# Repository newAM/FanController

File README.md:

## IR Fan Controller

### What is it?
This project is an Ethernet connected IR remote control for a the Seville classics ultra slimline tower fan, but it can be easily adapted to control other IR devices.  

### Why?
To connect my fan to Home Assistant so that it can turn on automatically when it gets hot, and turn off automatically when I leave home.

#### Why PoE?
Wireless home automation devices often make sense only when they are battery powered, if a power cable needs to be run it can carry data too.  Designing a low power wireless device is far more complicated than designing a wired device and running an Ethernet cable.

## Overview
Home Assistant → MQTT Broker → W5100 (Ethernet) → ATMega328P (MCU) → IR LED

The controller takes the states of the power, oscillation, mode, timer, and speed from Home Assistant.  These values are used to build the IR code then transmit it through the IR LED.

## Project Contents
* FanController_ArduinoCode - firmware for the ATMega328P
* FanController_Guide - reverse engineering guide for IR codes
* FanController_HomeAssistant - example Home Assistant configuration
* FanController_KiCAD - schematic and PCB
* FanController_Media - photos

## Software Used
* [KiCad](http://kicad.org/)
* [Arduino IDE](https://www.arduino.cc/en/Main/Software)
* [OpenSCAD](http://www.openscad.org/)
* [Libre Office](https://www.libreoffice.org/)
* [Home Assistant](https://www.home-assistant.io/)

### Arduino Libraries used
* [Arduino MQTT Client](https://github.com/knolleary/pubsubclient)

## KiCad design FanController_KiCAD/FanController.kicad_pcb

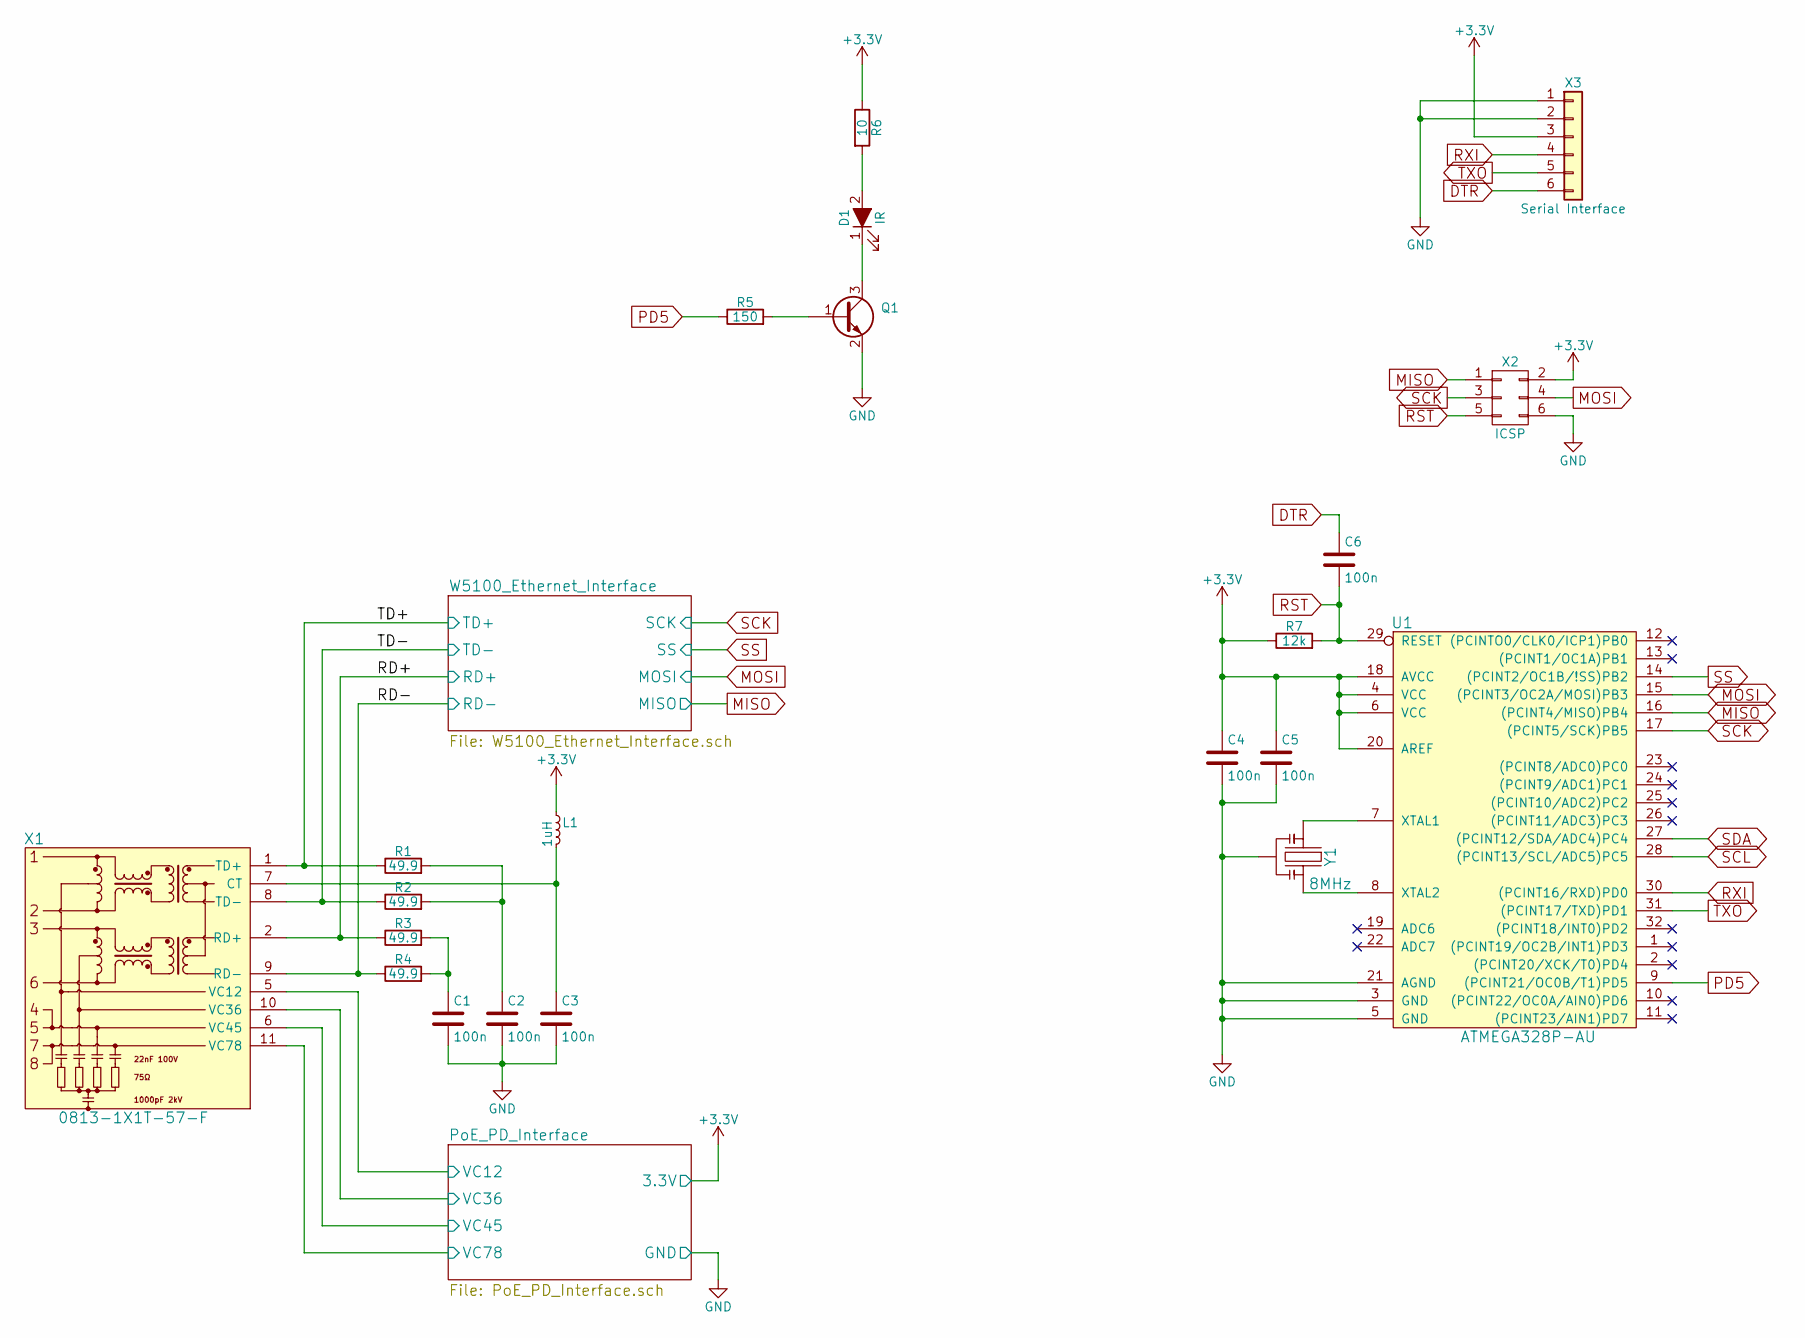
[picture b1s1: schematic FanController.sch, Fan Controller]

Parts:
C1, C2, C3, C4, C5, C6: 100n; C_0603; DigiKey Part Number 1276-1005-1-ND
D1: IR; LED_D5.0mm
L1: 1uH; C_0603; DigiKey Part Number 445-3163-1-ND
Q1: Q_NPN_BEC; SOT-23; DigiKey Part Number MMBT3904LT1GOSCT-ND
R1, R2, R3, R4: 49.9; R_0805; DigiKey Part Number RNCP0805FTD49R9CT-ND
R5: 150; R_0603; Tolerance 1%; DigiKey Part Number 311-150HRCT-ND
R6: 10; R_0805; DigiKey Part Number RNCP0805FTD10R0CT-ND
R7: 12k; R_0603; Tolerance 1%; DigiKey Part Number 311-12.0KHRCT-ND
U1: ATMEGA328P-AU; TQFP-32_7x7mm_Pitch0.8mm; DigiKey Part Number ATMEGA328P-AU-ND
X1: 0813-1X1T-57-F; 0813-1X1T-57-F_RJ45-Jack; DigiKey Part Number 507-1421-ND
X2: ICSP; Pin_Header_Straight_2x03_Pitch2.54mm
X3: Serial Interface; Pin_Header_Angled_1x06_Pitch2.54mm
Y1: 8MHz; CERALOCK_CSTCE_Resonator; DigiKey Part Number 490-1195-1-ND

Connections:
+3V3: C4.1, C5.1, L1.1, R6.1, R7.1, U1.4 (VCC), U1.6 (VCC), U1.18 (AVCC), U1.20 (AREF), X2.2, X3.3; also elsewhere on the board
/PoE_PD_Interface/VC12: X1.5 (VC12); also elsewhere on the board
/PoE_PD_Interface/VC36: X1.10 (VC36); also elsewhere on the board
/PoE_PD_Interface/VC45: X1.6 (VC45); also elsewhere on the board
/PoE_PD_Interface/VC78: X1.11 (VC78); also elsewhere on the board
/RD+: R3.1, X1.2 (RD+); also elsewhere on the board
/RD-: R4.1, X1.9 (RD-); also elsewhere on the board
/TD+: R1.1, X1.1 (TD+); also elsewhere on the board
/TD-: R2.1, X1.8 (TD-); also elsewhere on the board
DTR: C6.1, X3.6
GND: C1.2, C2.2, C3.2, C4.2, C5.2, Q1.2 (E), U1.3 (GND), U1.5 (GND), U1.21 (AGND), X2.6, X3.1, X3.2, Y1.2; also elsewhere on the board
MISO: U1.16 ((PCINT4/MISO)PB4), X2.1; also elsewhere on the board
MOSI: U1.15 ((PCINT3/OC2A/MOSI)PB3), X2.4; also elsewhere on the board
unnamed: C1.1, R3.2, R4.2
unnamed: C2.1, R1.2, R2.2
unnamed: C3.1, L1.2, X1.7 (CT)
unnamed: D1.1 (K), Q1.3 (C)
unnamed: D1.2 (A), R6.2
unnamed: Q1.1 (B), R5.2
unnamed: U1.7 (XTAL1), Y1.1
unnamed: U1.8 (XTAL2), Y1.3
PD5: R5.1, U1.9 ((PCINT21/OC0B/T1)PD5)
RST: C6.2, R7.2, U1.29 (RESET), X2.5
RXI: U1.30 ((PCINT16/RXD)PD0), X3.4
SCK: U1.17 ((PCINT5/SCK)PB5), X2.3; also elsewhere on the board
SS: U1.14 ((PCINT2/OC1B/!SS)PB2); also elsewhere on the board
TXO: U1.31 ((PCINT17/TXD)PD1), X3.5

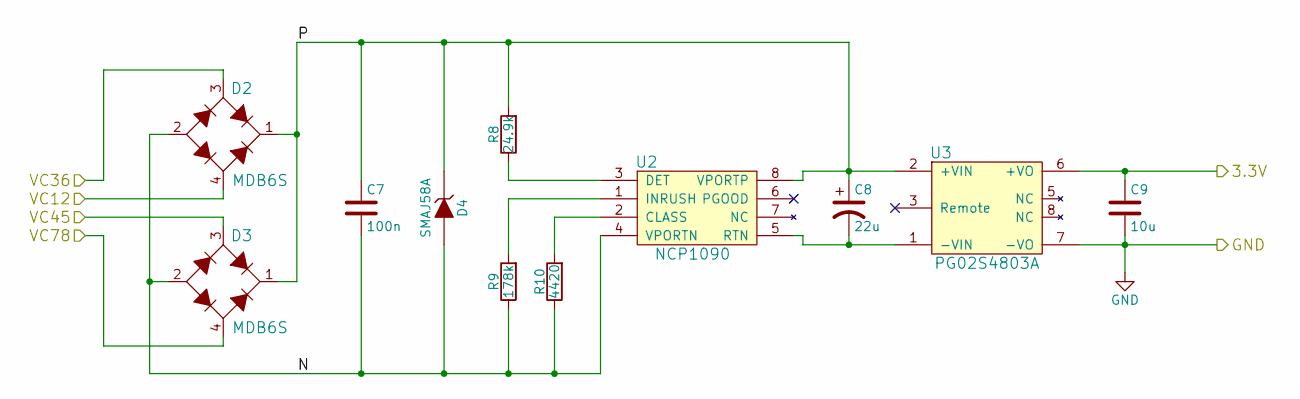
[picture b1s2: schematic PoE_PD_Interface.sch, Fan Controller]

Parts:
C7: 100n; C_0805; DigiKey Part Number 1276-6840-1-ND
C8: 22u; CP_Radial_D5.0mm_P2.00mm; DigiKey Part Number 493-12798-1-ND
C9: 10u; C_0805; DigiKey Part Number 1276-6456-1-ND
D2, D3: MDB6S; Micro-DIP-4; DigiKey Part Number MDB6SFSCT-ND
D4: SMAJ58A; D_SMA; DigiKey Part Number SMAJ58A-E3/61GICT-ND
R8: 24.9k; R_0603; DigiKey Part Number 311-24.9KHRCT-ND
R9: 178k; R_0603; DigiKey Part Number 311-178KHRCT-ND
R10: 4420; R_0603; DigiKey Part Number 311-4.42KHRCT-ND
U2: NCP1090; SOIC-8_3.9x4.9mm_Pitch1.27mm; DigiKey Part Number NCP1090DGOS-ND
U3: PG02S4803A; PG02S; DigiKey Part Number 941-1185-ND

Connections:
+3V3: C9.1, U3.6 (+VO); also elsewhere on the board
/PoE_PD_Interface/N: C7.2, D2.2 (-), D3.2 (-), D4.2 (A), R9.1, R10.1, U2.4 (VPORTN)
/PoE_PD_Interface/P: C7.1, C8.1, D2.1 (+), D3.1 (+), D4.1 (K), R8.2, U2.8 (VPORTP), U3.2 (+VIN)
/PoE_PD_Interface/VC12: D2.4 (AC2); also elsewhere on the board
/PoE_PD_Interface/VC36: D2.3 (AC1); also elsewhere on the board
/PoE_PD_Interface/VC45: D3.3 (AC1); also elsewhere on the board
/PoE_PD_Interface/VC78: D3.4 (AC2); also elsewhere on the board
GND: C9.2, U3.7 (-VO); also elsewhere on the board
unnamed: C8.2, U2.5 (RTN), U3.1 (-VIN)
unnamed: R8.1, U2.3 (DET)
unnamed: R9.2, U2.1 (INRUSH)
unnamed: R10.2, U2.2 (CLASS)

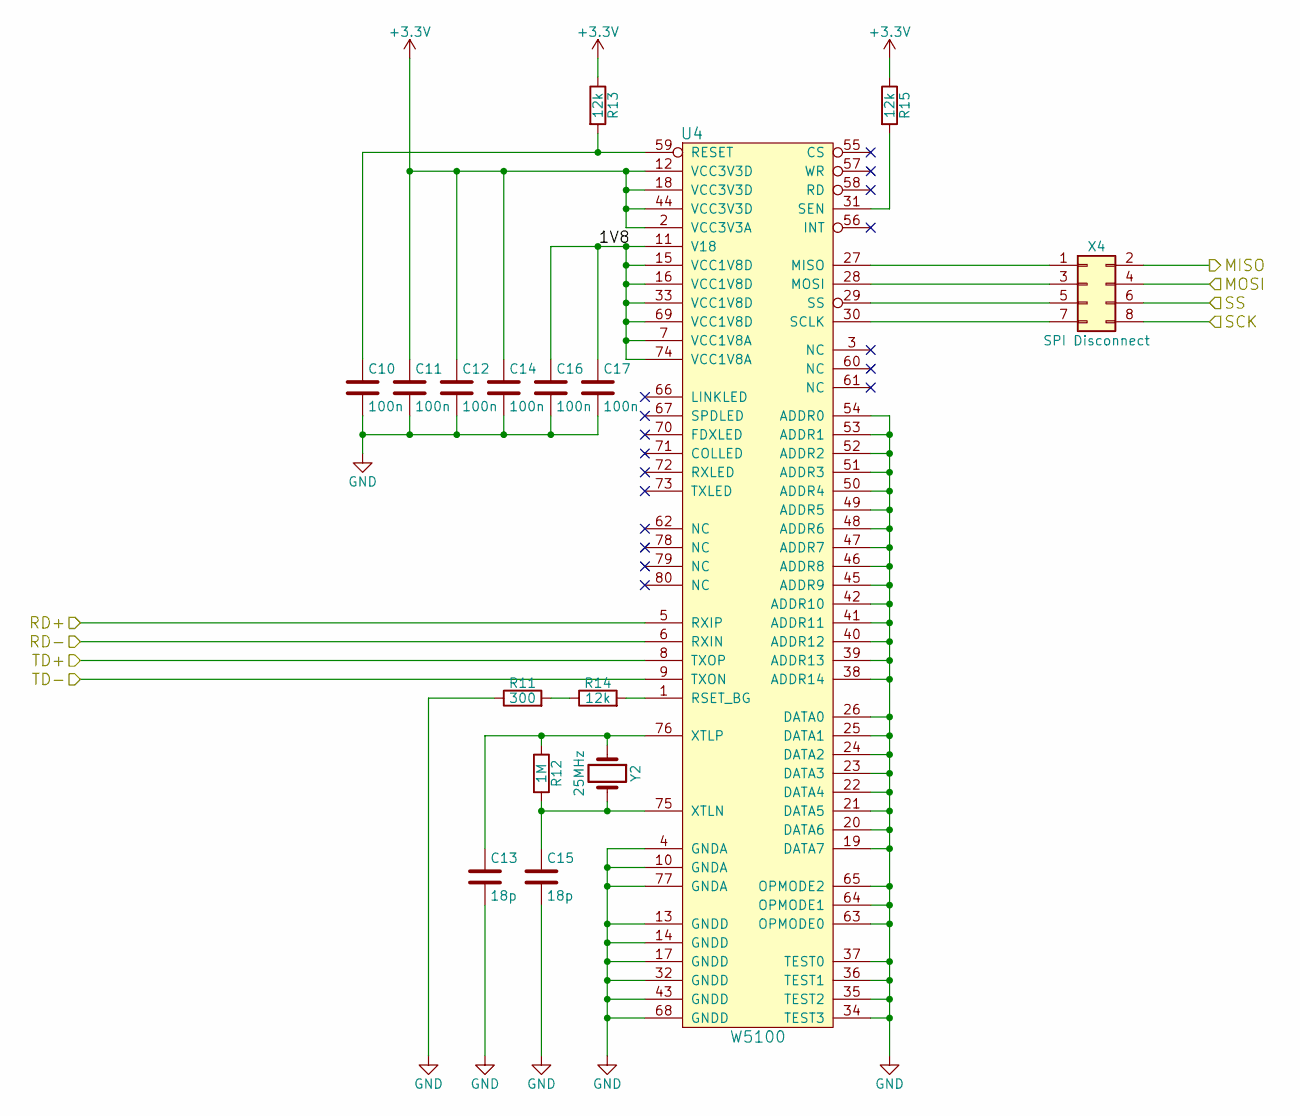
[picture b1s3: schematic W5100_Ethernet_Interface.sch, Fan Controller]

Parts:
C10, C11, C12, C14, C16, C17: 100n; C_0603; DigiKey Part Number 1276-1005-1-ND
C13, C15: 18p; C_0603; DigiKey Part Number 1276-1089-1-ND
R11: 300; R_0603; Tolerance 1%; DigiKey Part Number 311-300HRCT-ND
R12: 1M; R_0603; Tolerance 1%; DigiKey Part Number 311-1.00MHRCT-ND
R13, R14, R15: 12k; R_0603; Tolerance 1%; DigiKey Part Number 311-12.0KHRCT-ND
U4: W5100; LQFP-80_10x10mm_Pitch0.4mm; DigiKey Part Number 1278-1002-ND
X4: SPI Disconnect; Pin_Header_Straight_2x04_Pitch2.54mm
Y2: 25MHz; Crystal_SMD_HC49-SD; DigiKey Part Number 535-10235-1-ND

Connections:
+3V3: C11.1, C12.1, C14.1, R13.1, R15.1, U4.2 (VCC3V3A), U4.12 (VCC3V3D), U4.18 (VCC3V3D), U4.44 (VCC3V3D); also elsewhere on the board
/RD+: U4.5 (RXIP); also elsewhere on the board
/RD-: U4.6 (RXIN); also elsewhere on the board
/TD+: U4.8 (TXOP); also elsewhere on the board
/TD-: U4.9 (TXON); also elsewhere on the board
/W5100_Ethernet_Interface/1V8: C16.1, C17.1, U4.7 (VCC1V8A), U4.11 (V18), U4.15 (VCC1V8D), U4.16 (VCC1V8D), U4.33 (VCC1V8D), U4.69 (VCC1V8D), U4.74 (VCC1V8A)
GND: C10.2, C11.2, C12.2, C13.2, C14.2, C15.2, C16.2, C17.2, R11.1, U4.4 (GNDA), U4.10 (GNDA), U4.13 (GNDD), U4.14 (GNDD), U4.17 (GNDD), U4.19 (DATA7), U4.20 (DATA6), U4.21 (DATA5), U4.22 (DATA4), U4.23 (DATA3), U4.24 (DATA2), U4.25 (DATA1), U4.26 (DATA0), U4.32 (GNDD), U4.34 (TEST3), U4.35 (TEST2), U4.36 (TEST1), U4.37 (TEST0), U4.38 (ADDR14), U4.39 (ADDR13), U4.40 (ADDR12), U4.41 (ADDR11), U4.42 (ADDR10), U4.43 (GNDD), U4.45 (ADDR9), U4.46 (ADDR8), U4.47 (ADDR7), U4.48 (ADDR6), U4.49 (ADDR5), U4.50 (ADDR4), U4.51 (ADDR3), U4.52 (ADDR2), U4.53 (ADDR1), U4.54 (ADDR0), U4.63 (OPMODE0), U4.64 (OPMODE1), U4.65 (OPMODE2), U4.68 (GNDD), U4.77 (GNDA); also elsewhere on the board
MISO: X4.2; also elsewhere on the board
MOSI: X4.4; also elsewhere on the board
unnamed: C10.1, R13.2, U4.59 (RESET)
unnamed: C13.1, R12.1, U4.76 (XTLP), Y2.1
unnamed: C15.1, R12.2, U4.75 (XTLN), Y2.2
unnamed: R11.2, R14.1
unnamed: R14.2, U4.1 (RSET_BG)
unnamed: R15.2, U4.31 (SEN)
unnamed: U4.27 (MISO), X4.1
unnamed: U4.28 (MOSI), X4.3
unnamed: U4.29 (SS), X4.5
unnamed: U4.30 (SCLK), X4.7
SCK: X4.8; also elsewhere on the board
SS: X4.6; also elsewhere on the board

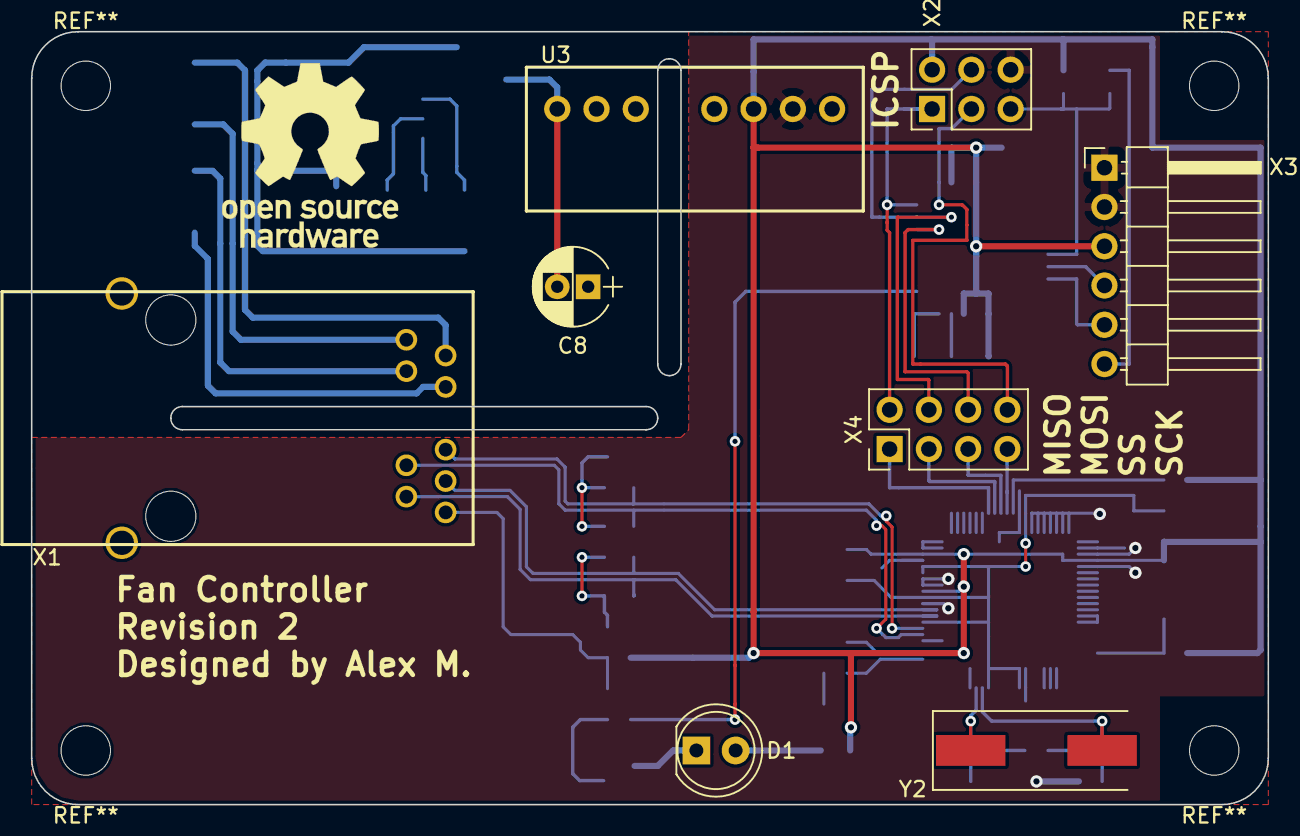
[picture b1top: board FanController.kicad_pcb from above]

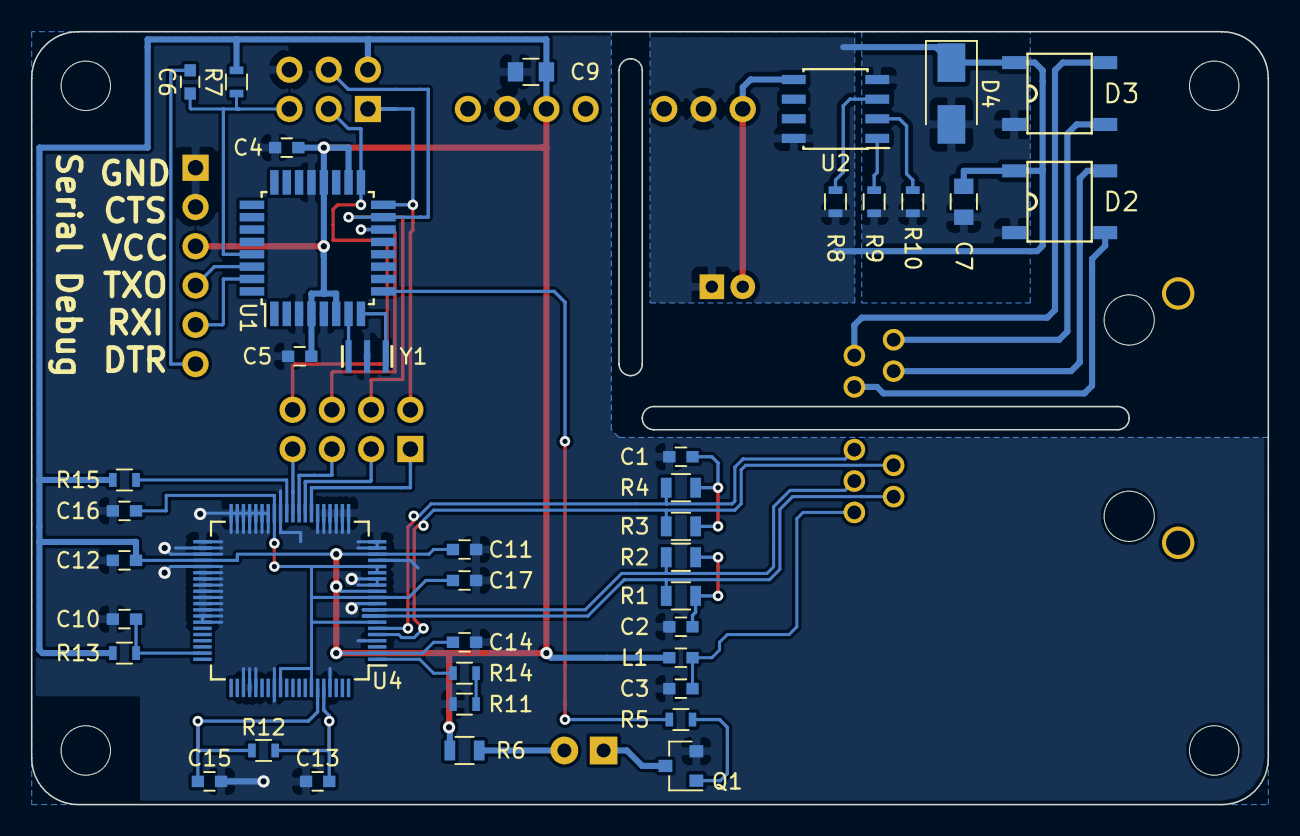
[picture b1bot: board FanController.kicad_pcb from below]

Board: 2 copper layers, 80.0 x 50.0 mm, 48 parts (40 on the bottom side), 44 nets.

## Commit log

2018-04-29 fixed md formatting
2018-05-07 fixed static control variable memory
2019-06-02 Added photos.
2020-04-26 Update some old python code that hurt to read.
2021-11-09 Update kicad URL
    https://forum.kicad.info/t/warning-avoid-all-links-to-kicad-pcb-org-use-kicad-org/31521
